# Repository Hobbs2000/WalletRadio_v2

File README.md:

# WalletRadio_v2
WalletRadio version 2. This version is no longer all analog, it uses a special radio receiver chip.

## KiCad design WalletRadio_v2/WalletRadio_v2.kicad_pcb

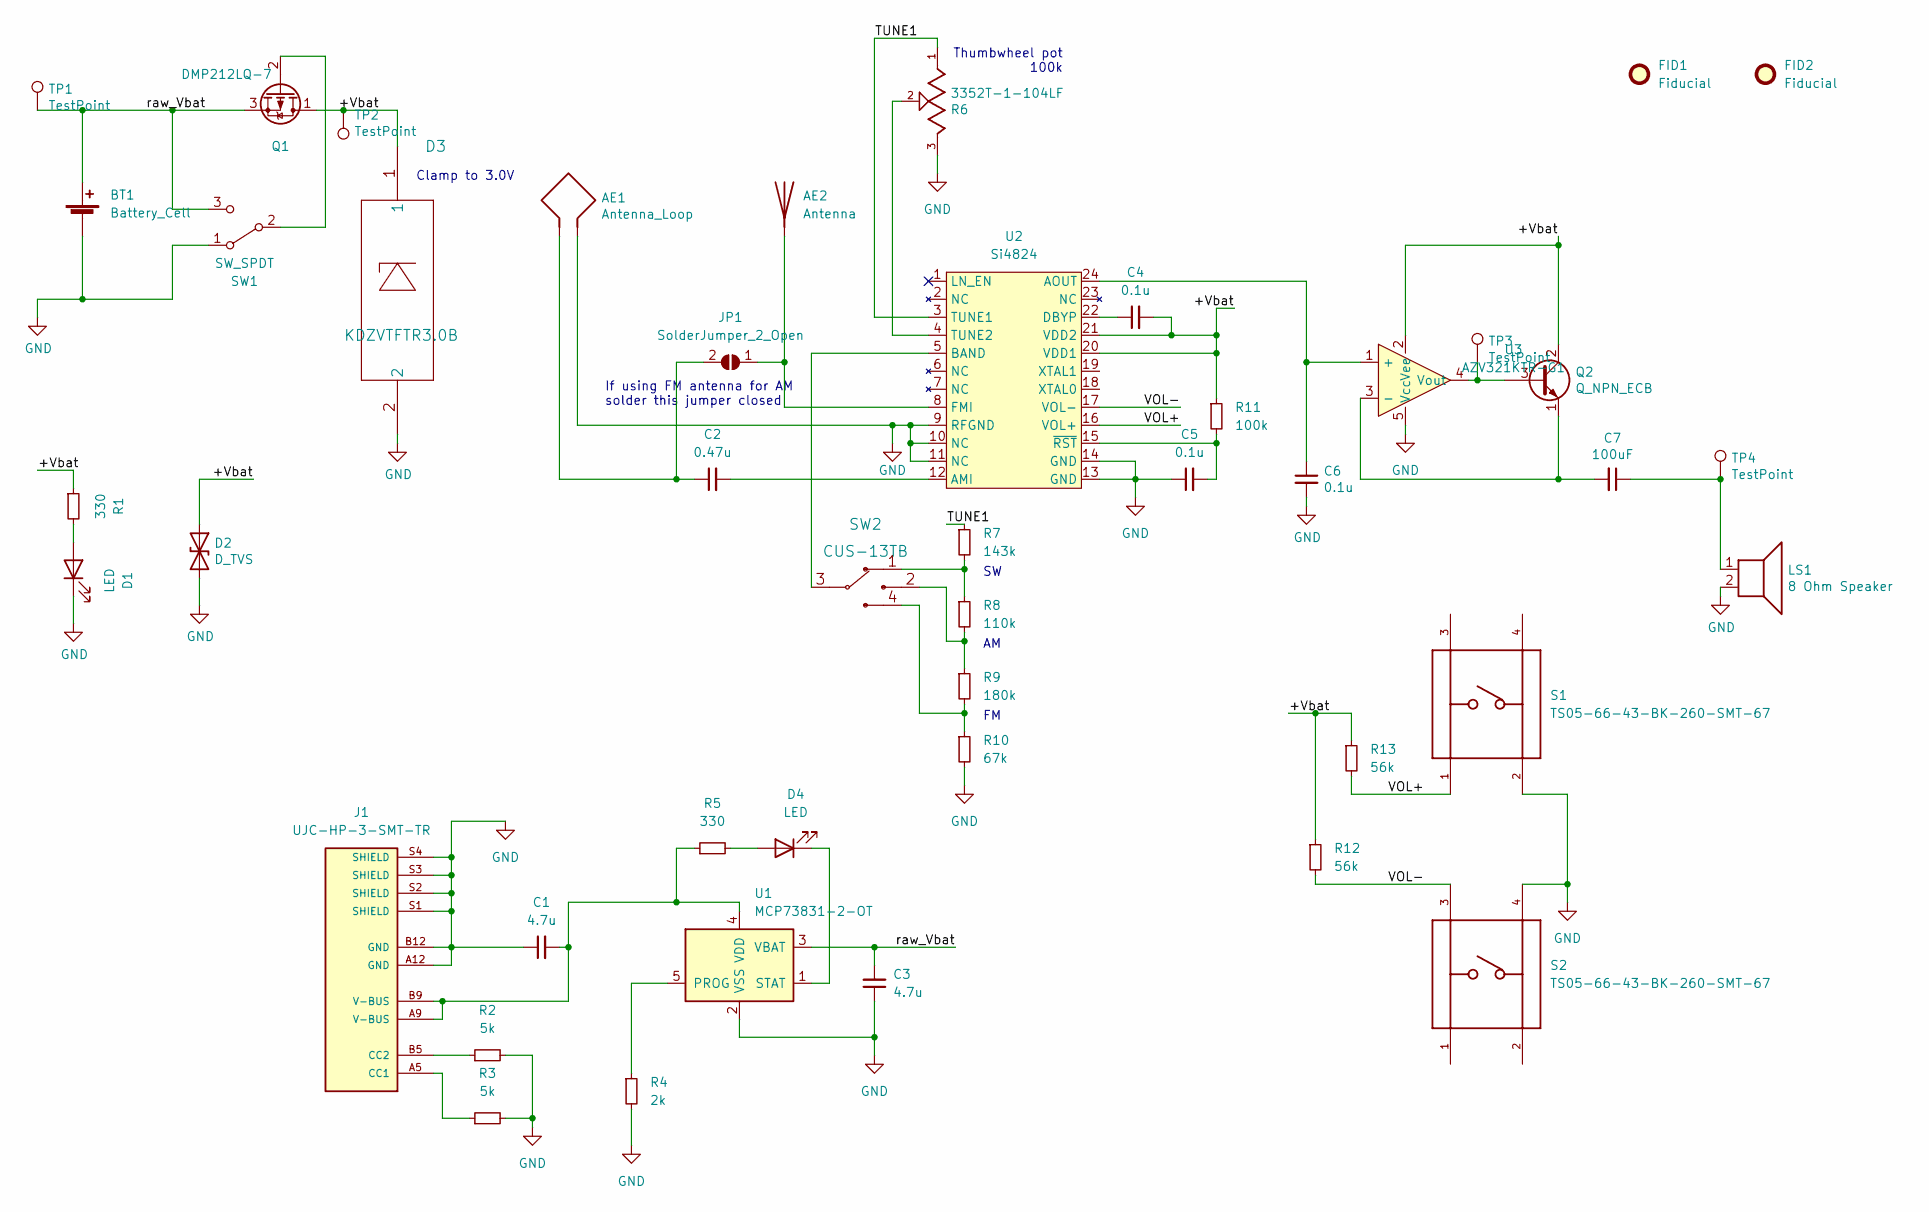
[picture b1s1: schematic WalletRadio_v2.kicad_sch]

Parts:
AE1: Antenna_Loop; Loop_Antenna
AE2: Antenna; FM_antenna
BT1: Battery_Cell; 1578_LiIon_Bat
C1, C3: 4.7u; C_0603_1608Metric_Pad1.08x0.95mm_HandSolder
C2: 0.47u; C_0603_1608Metric_Pad1.08x0.95mm_HandSolder
C4, C5, C6: 0.1u; C_0603_1608Metric_Pad1.08x0.95mm_HandSolder
C7: 100uF; C_1206_3216Metric_Pad1.33x1.80mm_HandSolder
D1, D4: LED; LED_0603_1608Metric_Pad1.05x0.95mm_HandSolder
D2: D_TVS; 5.0SMDJ9.0CA
D3: KDZVTFTR3.0B; KDZVTFTR3.3B
FID1, FID2: Fiducial; Fiducial_0.75mm_Mask2.25mm
J1: UJC-HP-3-SMT-TR; CUI_UJC-HP-3-SMT-TR; PARTREV 04/30/2020
JP1: SolderJumper_2_Open; SolderJumper-2_P1.3mm_Open_TrianglePad1.0x1.5mm
LS1: 8 Ohm Speaker; Wall
Q1: DMP212LQ-7; SOT-23_Handsoldering
Q2: Q_NPN_ECB; SOT-89-3_Handsoldering
R1, R5: 330; R_0603_1608Metric_Pad0.98x0.95mm_HandSolder
R2, R3: 5k; R_0603_1608Metric_Pad0.98x0.95mm_HandSolder
R4: 2k; R_0603_1608Metric_Pad0.98x0.95mm_HandSolder
R6: 3352T-1-104LF; TRIM_3352T-1-103LF; PARTREV 08/19
R7: 143k; R_0603_1608Metric_Pad0.98x0.95mm_HandSolder
R8: 110k; R_0603_1608Metric_Pad0.98x0.95mm_HandSolder
R9: 180k; R_0603_1608Metric_Pad0.98x0.95mm_HandSolder
R10: 67k; R_0603_1608Metric_Pad0.98x0.95mm_HandSolder
R11: 100k; R_0603_1608Metric_Pad0.98x0.95mm_HandSolder
R12, R13: 56k; R_0603_1608Metric_Pad0.98x0.95mm_HandSolder
S1, S2: TS05-66-43-BK-260-SMT-67; SW_TS05-66-43-BK-260-SMT-67; PARTREV 1.0
SW1: SW_SPDT; CUS-12TB_Switch
SW2: CUS-13TB
TP1, TP2, TP3, TP4: TestPoint; TestPoint_Pad_1.5x1.5mm
U1: MCP73831-2-OT; SOT-23-5
U2: Si4824; SSOP-24_3.9x8.7mm_P0.635mm
U3: AZV321KTR-G1; SOT-23-5

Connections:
/+Vbat: C4.2, D2.1 (A1), D3.1, Q1.1 (D), Q2.2 (C), R1.1, R11.1, R12.1, R13.1, TP2.1, U2.20 (VDD1), U2.21 (VDD2), U3.2 (Vee)
/TUNE1: R6.1, R7.1, U2.3 (TUNE1)
/VOL+: R13.2, S1.1, U2.16 (VOL+)
/VOL-: R12.2, S2.3, U2.17 (VOL-)
/raw_Vbat: BT1.1 (+), C3.2, Q1.3 (S), SW1.3 (C), TP1.1, U1.3 (VBAT)
GND: AE1.2, BT1.2 (-), C1.1, C3.1, C5.1, C6.2, D1.1 (K), D2.2 (A2), D3.2, J1.A12 (GND), J1.B12 (GND), J1.S1 (SHIELD), J1.S2 (SHIELD), J1.S3 (SHIELD), J1.S4 (SHIELD), LS1.2, R2.2, R3.2, R4.2, R6.3, R10.2, S1.2, S2.4, SW1.1 (A), U1.2 (VSS), U2.9 (RFGND), U2.10 (NC), U2.11 (NC), U2.13 (GND), U2.14 (GND), U3.5 (Vcc)
unnamed: AE1.1, C2.1, JP1.2 (B)
unnamed: AE2.1 (A), JP1.1 (A), U2.8 (FMI)
unnamed: C1.2, J1.A9 (V-BUS), J1.B9 (V-BUS), R5.1, U1.4 (VDD)
unnamed: C2.2, U2.12 (AMI)
unnamed: C4.1, U2.22 (DBYP)
unnamed: C5.2, R11.2, U2.15 (~RST)
unnamed: C6.1, U2.24 (AOUT), U3.1 (+)
unnamed: C7.1, LS1.1, TP4.1
unnamed: C7.2, Q2.1 (E), U3.3 (-)
unnamed: D1.2 (A), R1.2
unnamed: D4.1 (K), U1.1 (STAT)
unnamed: D4.2 (A), R5.2
unnamed: J1.A5 (CC1), R3.1
unnamed: J1.B5 (CC2), R2.1
unnamed: Q1.2 (G), SW1.2 (B)
unnamed: Q2.3 (B), TP3.1, U3.4 (Vout)
unnamed: R4.1, U1.5 (PROG)
unnamed: R6.2, U2.4 (TUNE2)
unnamed: R7.2, R8.1, SW2.1
unnamed: R8.2, R9.1, SW2.2
unnamed: R9.2, R10.1, SW2.4
unnamed: SW2.3, U2.5 (BAND)

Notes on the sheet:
If using FM antenna for AM solder this jumper closed
Clamp to 3.0V
Thumbwheel pot 100k

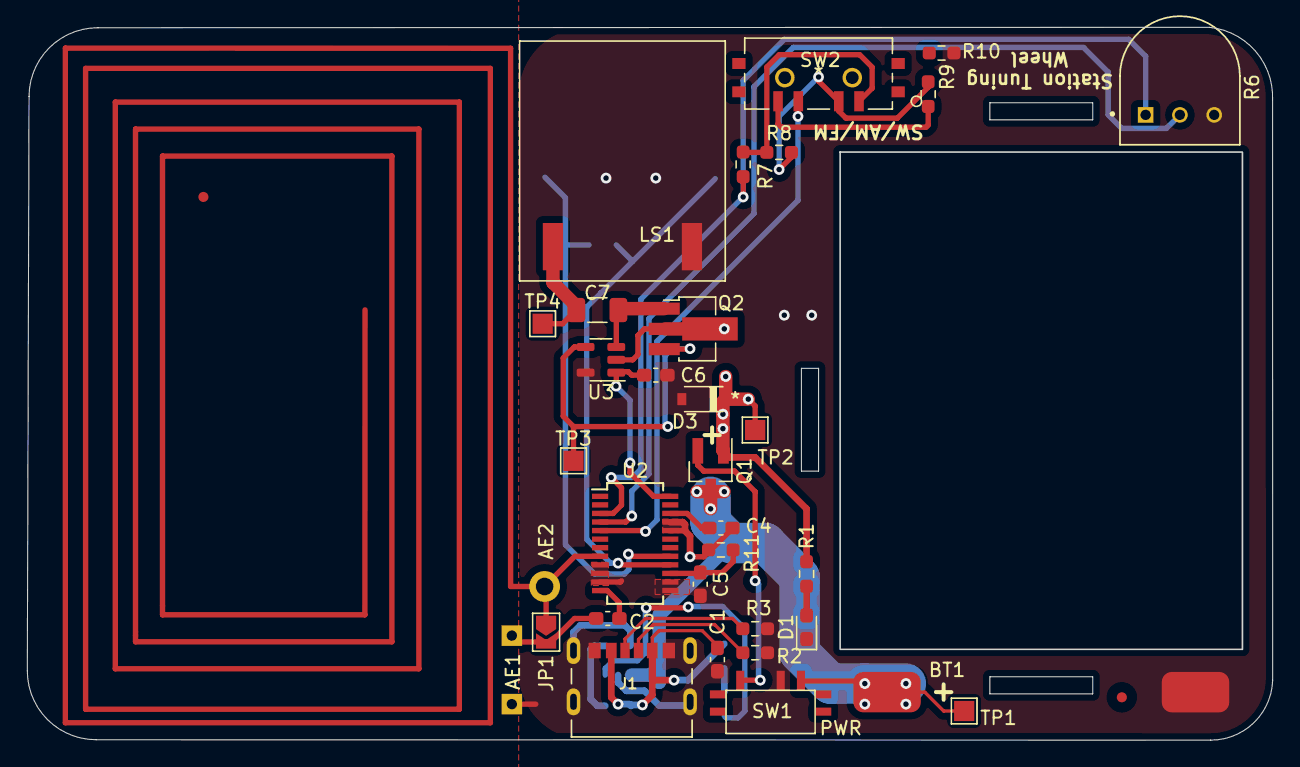
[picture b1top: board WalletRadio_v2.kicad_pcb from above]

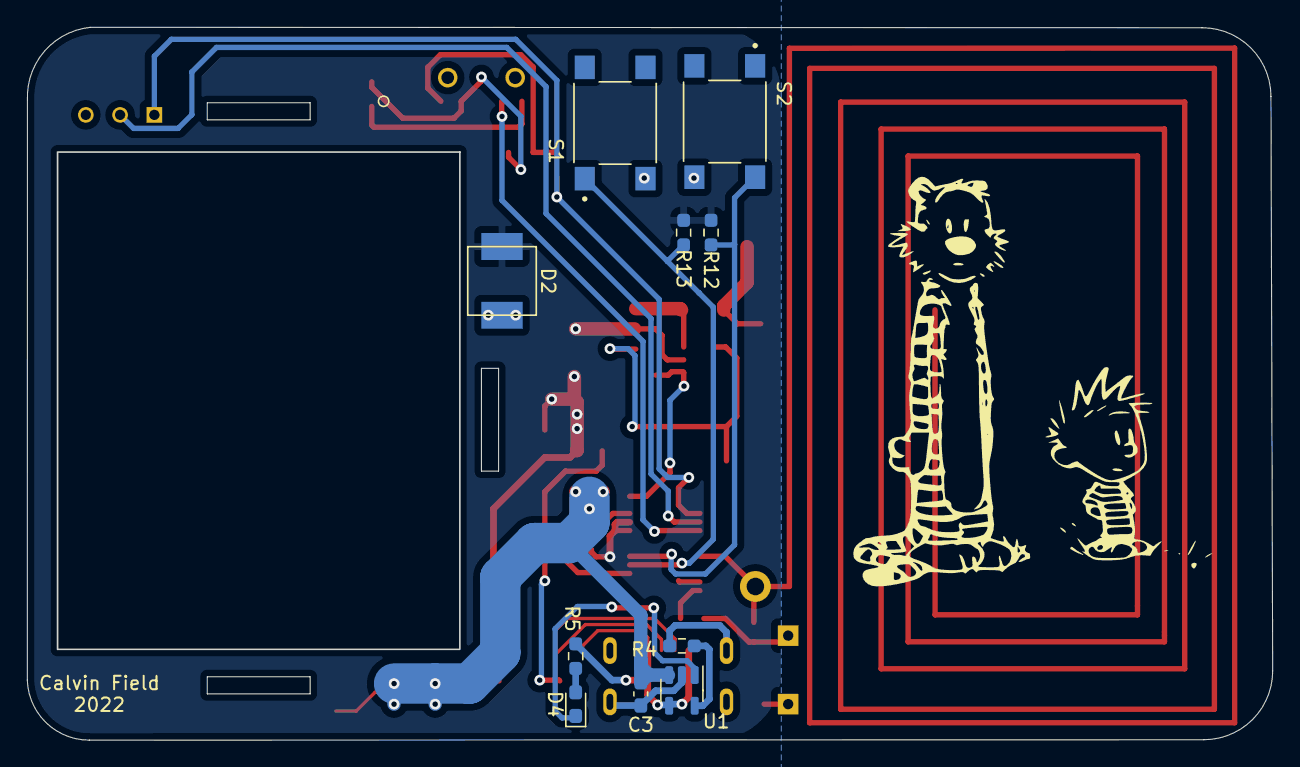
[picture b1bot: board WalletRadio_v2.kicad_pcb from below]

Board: 2 copper layers, 92.2 x 52.8 mm, 45 parts (10 on the bottom side), 28 nets.

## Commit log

2022-02-04 Added what I have done so far for the version 2
2022-02-04 Changed the coin cell holder. Redid entire PCB layout
2022-02-06 Added the remaining footprints for the components and continued laying out
2022-02-07 Did more layout
2022-02-09 Switched to LiIon battery; rerouted, also added battery charger w/ USB-C
2022-02-09 Added a zener diode clamp to ensure max 3.3V operating voltage on power rail
2022-02-10 Did more PCB layout.
2022-02-10 more layout
2022-02-11 More layout. Added fields for BOM creation.
2022-07-18 Had to change some components because they were out of stock
2022-07-19 Moved some stuff. Also added a graphic

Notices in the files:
parts and their libraries:
Copyright 2021 Accelerated Designs. All rights reserved.
